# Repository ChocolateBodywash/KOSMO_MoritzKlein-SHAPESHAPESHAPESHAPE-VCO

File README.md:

## KOSMO Format - SHAPE SHAPE SHAPE SHAPE VCO

A KOSMO format of Moritz Klein’s "Shapes VCO" with a few added features

The shapes VCO was probably one of the first synth projects I ever did, so this one is dear to my heart.
I love this VCO! Parts are easy to find, it stays in tune and it sounds awesome.

I felt I needed to push it further, the 40106 schmitt trigger inverter contains 6 inverters. What if I used all of them?
Well that was too much, but with the amount of op amps I needed I worked out 4 was the most I could get. I'm pretty sure it would be impossible to fit anymore without making this a massive 20cm module or something..

### Features

- For ease of use, there is one CV input that goes to a buffered multiple circuit. All four then get mixed into one output.

- Realizing it would be impossible to tune, I added a switch for each VCO. This also makes it easy to add or remove VCOs on the fly.

- Instead of a coarse tuning knob, I added an octave switch. This required a precision shunt voltage reference and a series of voltage dividers. The only catch was that it needed to be a negative voltage, so I inverted the whole thing. Problem solved.

- One easy win was adding a Look Mum No Computer link cable, this makes it compatible with the 1221 ocsilator expander. 

- The FM knob wouldn’t fit, so I used a trimpot instead. A compromise had to be made somewhere.

- There is also a center trimpot that acts like a coarse tuning knob just in case. All of these controls get summed together.

---
Note: This was created by a hobbyist with no formal engineering training outside various late night YouTube binges. 
I’ve confirmed these designs to work but I make no guarantees on the design working efficiently.. or working at all.

Additional credit: Analog Output (Richard Holmes) for footprint libraries and front panel templates.

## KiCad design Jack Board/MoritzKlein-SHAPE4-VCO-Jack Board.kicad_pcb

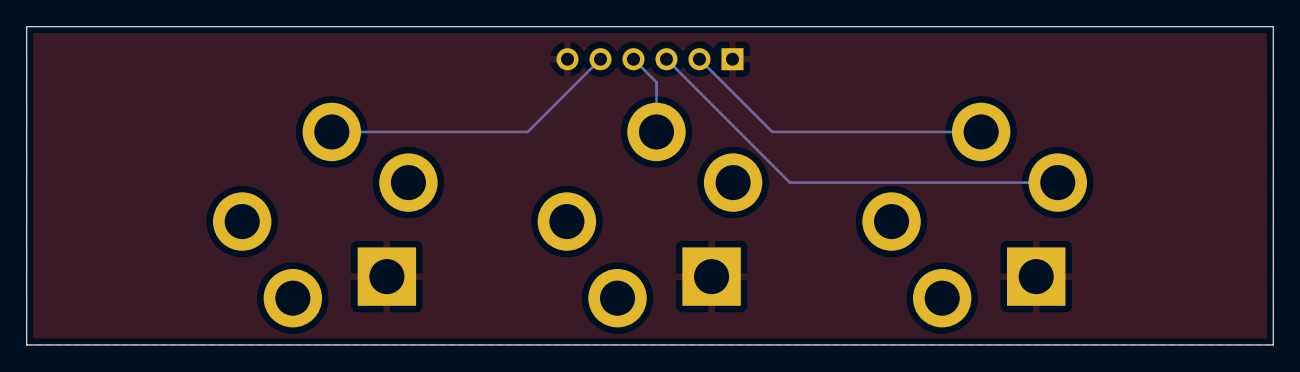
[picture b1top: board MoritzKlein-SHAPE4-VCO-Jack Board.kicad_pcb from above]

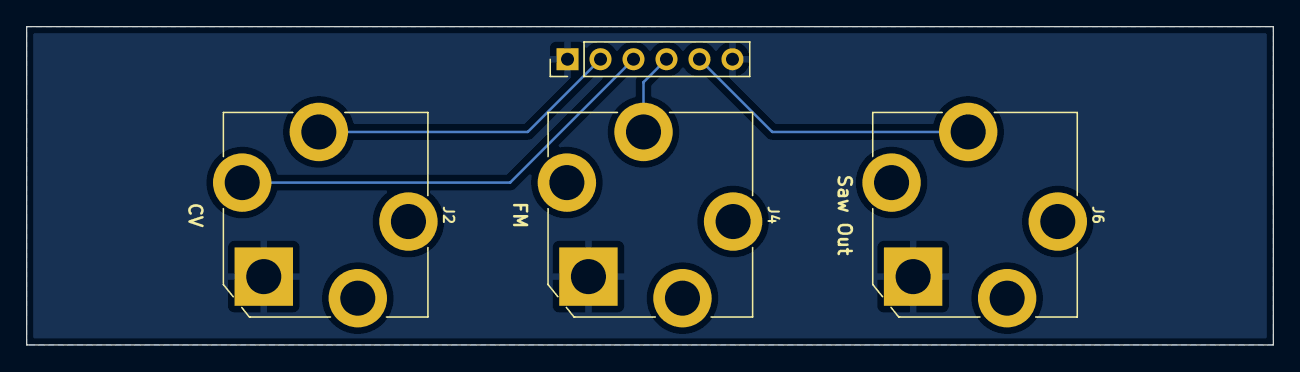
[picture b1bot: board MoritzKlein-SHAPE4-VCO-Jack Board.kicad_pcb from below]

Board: 2 copper layers, 96.0 x 24.5 mm, 4 parts (4 on the bottom side), 5 nets.

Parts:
J2: CV; Jack_6.35mm_PJ_629HAN
J3: 01x06_Pin; PinHeader_1x06_P2.54mm_Vertical_Centered
J4: FM; Jack_6.35mm_PJ_629HAN
J6: Saw Out; Jack_6.35mm_PJ_629HAN

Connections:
GND: J2.S, J3.1, J3.6, J4.S, J6.S
unnamed: J2.T, J3.2
unnamed: J2.TN, J3.3
unnamed: J3.4, J4.T
unnamed: J3.5, J6.T

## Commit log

2025-10-05 Upload+
2025-10-05 remove extra
2025-10-27 Update image
2026-05-28 Gerbers Added
